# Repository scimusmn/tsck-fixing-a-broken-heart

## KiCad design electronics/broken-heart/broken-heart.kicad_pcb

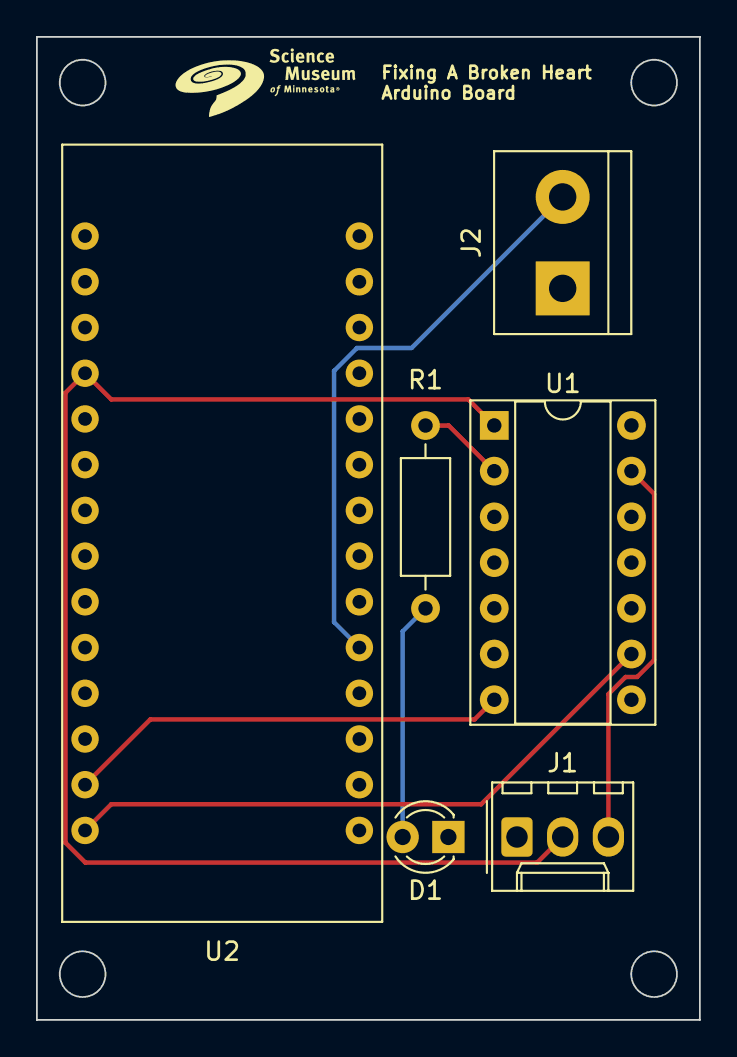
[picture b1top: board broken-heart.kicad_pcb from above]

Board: 2 copper layers, 36.8 x 54.6 mm, 6 parts (0 on the bottom side), 8 nets.

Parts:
D1: LED_D3.0mm
J1: KK-1x03
J2: Screw_Terminal_01x02; TerminalBlock-2_P5.08mm_small
R1: Resistor_L6.3mm_D2.5mm_P10.16mm_Horizontal
U1: DIP-14_W7.62mm_Socket
U2: Adafruit_Metro_Mini; Metro-Mini

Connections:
/RFID Reader/+5V: J1.2, U1.1 (VCC), U2.4 (5V)
/RFID Reader/GND: D1.1 (K), J1.1, J2.1, U1.14 (GND), U2.5 (GND)
/RFID Reader/SCK: U1.9 (PA4), U2.14 (A5)
/RFID Reader/SDA: U1.7 (PA6), U2.13 (A4)
unnamed: D1.2 (A), R1.2
unnamed: J1.3, U1.13 (AREF/PA0)
unnamed: J2.2, U2.19 (D4)
unnamed: R1.1, U1.2 (XTAL1/PB0)

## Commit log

2022-05-09 clean swap files
2022-05-09 create basic working arduino program
